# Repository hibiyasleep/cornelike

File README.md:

# Cornel

yet another [Crkbd](https://github.com/foostan/crkbd) clone, but with 5 rows.

---

<details>
<summary> Disclaimer </summary>

 ignore this if you're brave enough, like, if you know what Kailh Choc is, then
you are safe.

>  THIS PROJECT IS CURRENTLY WORK IN PROGRESS, NOTHING IS CLEAR, EVERY SPECIFICA-
> TION and/or DIMENSIONS and/or FEATURES and EVERYTHING MIGHT BE ABLE TO CHANGED
> WITHOUT ANY NOTICE. THIS MIGHT NOT FIT WITH YOUR LASER-ETCHED PLATE. THIS MIGHT
> DOES NOT FIT INTO YOUR $400 ALUMINUM CNC-ANODIZED CORNE CASE. YOUR CR2 BATTERY
> MIGHT BE BLOWN (SURE, I ALSO HAVE THIS RISK IN THIS CASE)
>
>  SO ANYWAY, I, HIBIYA INEMURI, DO NOT HOLD ANY TYPE OF RESPONSIBILITY IN ANY
> CASE.

</details>

## About

 According to [Crkbd](https://github.com/foostan/crkbd), the Corne keyboard is:

>  The Corne keyboard is a split keyboard with 3x6 column staggered keys and 3
> thumb keys, based on Helix. Crkbd stands for Corne Keyboard.

 Corne**l** is basically a clone of Corne keyboard, but with

* **Kailh Choc Switches** but keeping cherry pitch (19mm) for V2 keycaps.
* **Number Row**: to provide easy transition to 40% layout.
  can be removed later if no longer required. (irreversible)
* **Bluetooth MCU Support**: Cornel provides battery board (discharge only)
  that fits onto MCU cover, might be able to power [BLE Micro Pro](https://github.com/sekigon-gonnoc/BLE-Micro-Pro/), etc.
* **Low Profile**: Cornel might do any attempt to reduce thickness of keyboard.
  (TBD)

## Progress

* [ ] PCB
  * [x] Choc (revision: 1)
  * [ ] Cherry
* [ ] Plate
  * [ ] Upper (with acrylic and countersink holes)
  * [ ] Lower
* [ ] Software
  * [x] Arduino Demo (TBA)
  * [ ] QMK support
* [ ] Compability
  * [ ] Classic Pro Micro
  * [ ] [BLE Pro Micro](https://github.com/sekigon-gonnoc/BLE-Micro-Pro)
    * [ ] [LPME-IO](https://github.com/sekigon-gonnoc/LPME-IO)...?
  * [ ] [nice!nano](https://docs.nicekeyboards.com/)
  * [ ] TBA
* [ ] Problems
  * [ ] Detachability of Number row
  * [ ] removing LED Signal Skip jumper (by reordering LEDs)
* [ ] Photos

## Photos

> **WORK IN PROGRESS**

* First prototype (revision 0), with lubed 35g Burnt Orange.

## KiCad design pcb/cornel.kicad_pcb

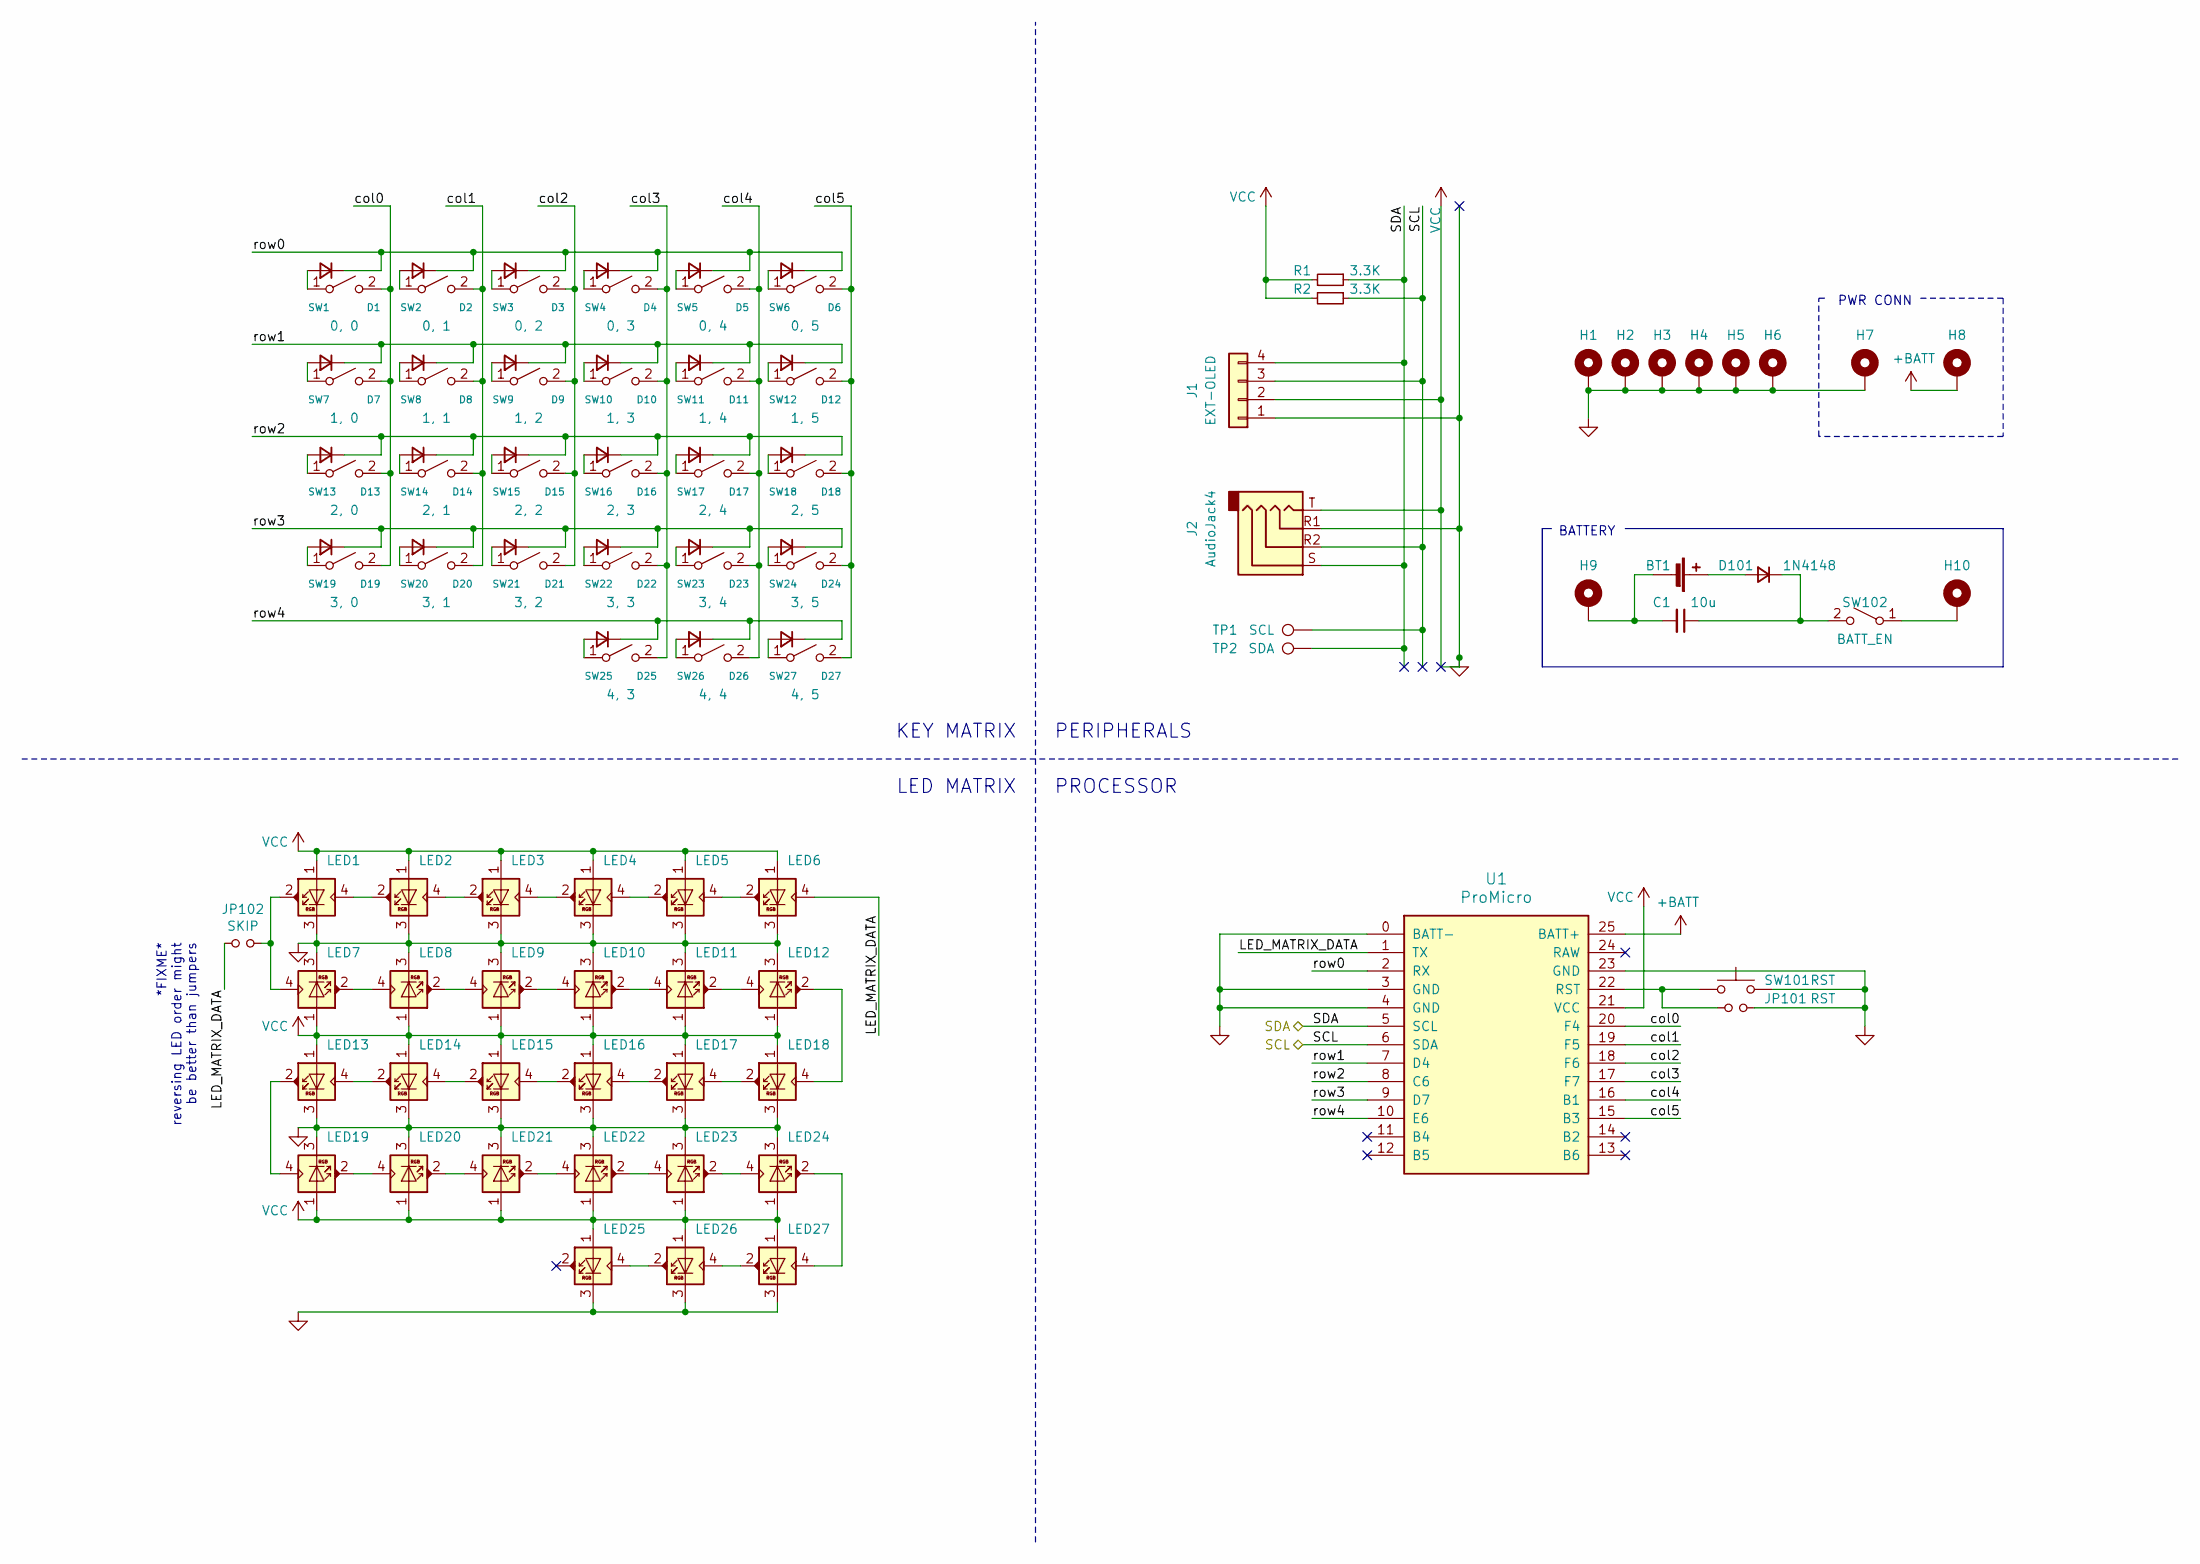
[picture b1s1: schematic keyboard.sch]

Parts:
BT1: CR1632; keystone-1010-mid-mount-cr2
C1: 10u; C_1206_3216Metric
D1, D2, D3, D4, D5, D6, D7, D8, D9, D10, D11, D12, D13, D14, D15, D16, D17, D18, D19, D20, D21, D22, D23, D24, D25, D26, D27, D101: 1N4148; D_1206_3216Metric
H1, H2, H3, H4, H5, H6: MountingHole_Pad; MountingHole_4.1mm_M2-Pillar_Pad
H7, H8, H9, H10: MountingHole_Pad; MountingHole_2.2mm_Via
J1: EXT-OLED; PinHeader_1x04_P2.54mm_Vertical
J2: AudioJack4; Jack_3.5mm_PJ320A_Horizontal
JP101: RST; SolderJumper-2_P1.3mm_Open_Pad1.0x1.5mm
JP102: SKIP; SolderJumper-2_P1.3mm_Open_Pad1.0x1.5mm
LED1, LED2, LED3, LED4, LED5, LED6, LED7, LED8, LED9, LED10, LED11, LED12, LED13, LED14, LED15, LED16, LED17, LED18, LED19, LED20, LED21, LED22, LED23, LED24, LED25, LED26, LED27: SK6812MINI; SK6812MINI-E_InsidePCB_singleside
R1, R2: 3.3K; R_1206_3216Metric
SW1: 0, 0; kailh-pcb-socket-choc-singleside
SW2: 0, 1; kailh-pcb-socket-choc-singleside
SW3: 0, 2; kailh-pcb-socket-choc-singleside
SW4: 0, 3; kailh-pcb-socket-choc-singleside
SW5: 0, 4; kailh-pcb-socket-choc-singleside
SW6: 0, 5; kailh-pcb-socket-choc-singleside
SW7: 1, 0; kailh-pcb-socket-choc-singleside
SW8: 1, 1; kailh-pcb-socket-choc-singleside
SW9: 1, 2; kailh-pcb-socket-choc-singleside
SW10: 1, 3; kailh-pcb-socket-choc-singleside
SW11: 1, 4; kailh-pcb-socket-choc-singleside
SW12: 1, 5; kailh-pcb-socket-choc-singleside
SW13: 2, 0; kailh-pcb-socket-choc-singleside
SW14: 2, 1; kailh-pcb-socket-choc-singleside
SW15: 2, 2; kailh-pcb-socket-choc-singleside
SW16: 2, 3; kailh-pcb-socket-choc-singleside
SW17: 2, 4; kailh-pcb-socket-choc-singleside
SW18: 2, 5; kailh-pcb-socket-choc-singleside
SW19: 3, 0; kailh-pcb-socket-choc-singleside
SW20: 3, 1; kailh-pcb-socket-choc-singleside
SW21: 3, 2; kailh-pcb-socket-choc-singleside
SW22: 3, 3; kailh-pcb-socket-choc-singleside
SW23: 3, 4; kailh-pcb-socket-choc-singleside
SW24: 3, 5; kailh-pcb-socket-choc-singleside
SW25: 4, 3; kailh-pcb-socket-choc-singleside
SW26: 4, 4; kailh-pcb-socket-choc-singleside
SW27: 4, 5; kailh-pcb-socket-choc-singleside
SW101: RST; SW_Push_SPST_NO_Alps_SKRK
SW102: BATT_EN; K3-1296S
TP1: SCL
TP2: SDA
U1: ProMicro; arduino-pro-micro-with-batt

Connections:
+BATT: H8.1, U1.25 (BATT+); also elsewhere on the board
/keyboard-l/LED_MATRIX_DATA: JP102.2, LED6.4 (DIN), U1.1 (TX)
/keyboard-l/SCL: J1.3, J2.R2, R2.1, U1.6 (SDA)
/keyboard-l/SDA: J1.4, J2.S, R1.1, U1.5 (SCL)
/keyboard-l/col0: SW1.2 (B), SW7.2 (B), SW13.2 (B), SW19.2 (B), U1.20 (F4)
/keyboard-l/col1: SW2.2 (B), SW8.2 (B), SW14.2 (B), SW20.2 (B), U1.19 (F5)
/keyboard-l/col2: SW3.2 (B), SW9.2 (B), SW15.2 (B), SW21.2 (B), U1.18 (F6)
/keyboard-l/col3: SW4.2 (B), SW10.2 (B), SW16.2 (B), SW22.2 (B), SW25.2 (B), U1.17 (F7)
/keyboard-l/col4: SW5.2 (B), SW11.2 (B), SW17.2 (B), SW23.2 (B), SW26.2 (B), U1.16 (B1)
/keyboard-l/col5: SW6.2 (B), SW12.2 (B), SW18.2 (B), SW24.2 (B), SW27.2 (B), U1.15 (B3)
/keyboard-l/row0: D1.1 (K), D2.1 (K), D3.1 (K), D4.1 (K), D5.1 (K), D6.1 (K), U1.2 (RX)
/keyboard-l/row1: D7.1 (K), D8.1 (K), D9.1 (K), D10.1 (K), D11.1 (K), D12.1 (K), U1.7 (D4)
/keyboard-l/row2: D13.1 (K), D14.1 (K), D15.1 (K), D16.1 (K), D17.1 (K), D18.1 (K), U1.8 (C6)
/keyboard-l/row3: D19.1 (K), D20.1 (K), D21.1 (K), D22.1 (K), D23.1 (K), D24.1 (K), U1.9 (D7)
/keyboard-l/row4: D25.1 (K), D26.1 (K), D27.1 (K), U1.10 (E6)
unnamed: BT1.1 (+), D101.2 (A)
unnamed: BT1.2 (-), C1.2, H9.1
unnamed: C1.1, D101.1 (K), SW102.2 (B)
unnamed: D1.2 (A), SW1.1 (A)
unnamed: D2.2 (A), SW2.1 (A)
unnamed: D3.2 (A), SW3.1 (A)
unnamed: D4.2 (A), SW4.1 (A)
unnamed: D5.2 (A), SW5.1 (A)
unnamed: D6.2 (A), SW6.1 (A)
unnamed: D7.2 (A), SW7.1 (A)
unnamed: D8.2 (A), SW8.1 (A)
unnamed: D9.2 (A), SW9.1 (A)
unnamed: D10.2 (A), SW10.1 (A)
unnamed: D11.2 (A), SW11.1 (A)
unnamed: D12.2 (A), SW12.1 (A)
unnamed: D13.2 (A), SW13.1 (A)
unnamed: D14.2 (A), SW14.1 (A)
unnamed: D15.2 (A), SW15.1 (A)
unnamed: D16.2 (A), SW16.1 (A)
unnamed: D17.2 (A), SW17.1 (A)
unnamed: D18.2 (A), SW18.1 (A)
unnamed: D19.2 (A), SW19.1 (A)
unnamed: D20.2 (A), SW20.1 (A)
unnamed: D21.2 (A), SW21.1 (A)
unnamed: D22.2 (A), SW22.1 (A)
unnamed: D23.2 (A), SW23.1 (A)
unnamed: D24.2 (A), SW24.1 (A)
unnamed: D25.2 (A), SW25.1 (A)
unnamed: D26.2 (A), SW26.1 (A)
unnamed: D27.2 (A), SW27.1 (A)
unnamed: H10.1, SW102.1 (A)
unnamed: SW101.2, U1.22 (RST)
unnamed: JP102.1, LED1.2 (DOUT), LED7.4 (DIN)
unnamed: LED1.4 (DIN), LED2.2 (DOUT)
unnamed: LED2.4 (DIN), LED3.2 (DOUT)
unnamed: LED3.4 (DIN), LED4.2 (DOUT)
unnamed: LED4.4 (DIN), LED5.2 (DOUT)
unnamed: LED5.4 (DIN), LED6.2 (DOUT)
unnamed: LED7.2 (DOUT), LED8.4 (DIN)
unnamed: LED8.2 (DOUT), LED9.4 (DIN)
unnamed: LED10.2 (DOUT), LED11.4 (DIN)
unnamed: LED9.2 (DOUT), LED10.4 (DIN)
unnamed: LED11.2 (DOUT), LED12.4 (DIN)
unnamed: LED12.2 (DOUT), LED18.4 (DIN)
unnamed: LED13.2 (DOUT), LED19.4 (DIN)
unnamed: LED13.4 (DIN), LED14.2 (DOUT)
unnamed: LED14.4 (DIN), LED15.2 (DOUT)
unnamed: LED15.4 (DIN), LED16.2 (DOUT)
unnamed: LED16.4 (DIN), LED17.2 (DOUT)
unnamed: LED17.4 (DIN), LED18.2 (DOUT)
unnamed: LED19.2 (DOUT), LED20.4 (DIN)
unnamed: LED20.2 (DOUT), LED21.4 (DIN)
unnamed: LED21.2 (DOUT), LED22.4 (DIN)
unnamed: LED22.2 (DOUT), LED23.4 (DIN)
unnamed: LED23.2 (DOUT), LED24.4 (DIN)
unnamed: LED24.2 (DOUT), LED27.4 (DIN)
unnamed: LED25.4 (DIN), LED26.2 (DOUT)
unnamed: LED26.4 (DIN), LED27.2 (DOUT)

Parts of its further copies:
BT2, BT3: CR1632; keystone-1010-mid-mount-cr2
C2: 10u; C_1206_3216Metric
D28, D29, D30, D31, D32, D33, D34, D35, D36, D37, D38, D39, D40, D41, D42, D43, D44, D45, D46, D47, D48, D49, D50, D51, D52, D53, D54, D201: 1N4148; D_1206_3216Metric
H11, H12, H13, H14, H15, H16: MountingHole_Pad; MountingHole_4.1mm_M2-Pillar_Pad
H17, H18, H19, H20: MountingHole_Pad; MountingHole_2.2mm_Via
J3: EXT-OLED; PinHeader_1x04_P2.54mm_Vertical
J4: AudioJack4; Jack_3.5mm_PJ320A_Horizontal
JP201: RST; SolderJumper-2_P1.3mm_Open_Pad1.0x1.5mm
JP202: SKIP; SolderJumper-2_P1.3mm_Open_Pad1.0x1.5mm
LED28, LED29, LED30, LED31, LED32, LED33, LED34, LED35, LED36, LED37, LED38, LED39, LED40, LED41, LED42, LED43, LED44, LED45, LED46, LED47, LED48, LED49, LED50, LED51, LED52, LED53, LED54: SK6812MINI; SK6812MINI-E_InsidePCB_singleside
R3, R4: 3.3K; R_1206_3216Metric
SW28: 0, 0; kailh-pcb-socket-choc-singleside
SW29: 0, 1; kailh-pcb-socket-choc-singleside
SW30: 0, 2; kailh-pcb-socket-choc-singleside
SW31: 0, 3; kailh-pcb-socket-choc-singleside
SW32: 0, 4; kailh-pcb-socket-choc-singleside
SW33: 0, 5; kailh-pcb-socket-choc-singleside
SW34: 1, 0; kailh-pcb-socket-choc-singleside
SW35: 1, 1; kailh-pcb-socket-choc-singleside
SW36: 1, 2; kailh-pcb-socket-choc-singleside
SW37: 1, 3; kailh-pcb-socket-choc-singleside
SW38: 1, 4; kailh-pcb-socket-choc-singleside
SW39: 1, 5; kailh-pcb-socket-choc-singleside
SW40: 2, 0; kailh-pcb-socket-choc-singleside
SW41: 2, 1; kailh-pcb-socket-choc-singleside
SW42: 2, 2; kailh-pcb-socket-choc-singleside
SW43: 2, 3; kailh-pcb-socket-choc-singleside
SW44: 2, 4; kailh-pcb-socket-choc-singleside
SW45: 2, 5; kailh-pcb-socket-choc-singleside
SW46: 3, 0; kailh-pcb-socket-choc-singleside
SW47: 3, 1; kailh-pcb-socket-choc-singleside
SW48: 3, 2; kailh-pcb-socket-choc-singleside
SW49: 3, 3; kailh-pcb-socket-choc-singleside
SW50: 3, 4; kailh-pcb-socket-choc-singleside
SW51: 3, 5; kailh-pcb-socket-choc-singleside
SW52: 4, 3; kailh-pcb-socket-choc-singleside
SW53: 4, 4; kailh-pcb-socket-choc-singleside
SW54: 4, 5; kailh-pcb-socket-choc-singleside
SW201: RST; SW_Push_SPST_NO_Alps_SKRK
SW202: BATT_EN; K3-1296S
TP3: SCL
TP4: SDA
U2: ProMicro; arduino-pro-micro-with-batt

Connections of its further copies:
+BATT: H18.1, U2.25 (BATT+); also elsewhere on the board
/keyboard-r/LED_MATRIX_DATA: JP202.2, LED33.4 (DIN), U2.1 (TX)
/keyboard-r/SCL: J3.3, J4.R2, R4.1, U2.6 (SDA)
/keyboard-r/SDA: J3.4, J4.S, R3.1, U2.5 (SCL)
/keyboard-r/col0: SW28.2 (B), SW34.2 (B), SW40.2 (B), SW46.2 (B), U2.20 (F4)
/keyboard-r/col1: SW29.2 (B), SW35.2 (B), SW41.2 (B), SW47.2 (B), U2.19 (F5)
/keyboard-r/col2: SW30.2 (B), SW36.2 (B), SW42.2 (B), SW48.2 (B), U2.18 (F6)
/keyboard-r/col3: SW31.2 (B), SW37.2 (B), SW43.2 (B), SW49.2 (B), SW52.2 (B), U2.17 (F7)
/keyboard-r/col4: SW32.2 (B), SW38.2 (B), SW44.2 (B), SW50.2 (B), SW53.2 (B), U2.16 (B1)
/keyboard-r/col5: SW33.2 (B), SW39.2 (B), SW45.2 (B), SW51.2 (B), SW54.2 (B), U2.15 (B3)
/keyboard-r/row0: D28.1 (K), D29.1 (K), D30.1 (K), D31.1 (K), D32.1 (K), D33.1 (K), U2.2 (RX)
/keyboard-r/row1: D34.1 (K), D35.1 (K), D36.1 (K), D37.1 (K), D38.1 (K), D39.1 (K), U2.7 (D4)
/keyboard-r/row2: D40.1 (K), D41.1 (K), D42.1 (K), D43.1 (K), D44.1 (K), D45.1 (K), U2.8 (C6)
/keyboard-r/row3: D46.1 (K), D47.1 (K), D48.1 (K), D49.1 (K), D50.1 (K), D51.1 (K), U2.9 (D7)
/keyboard-r/row4: D52.1 (K), D53.1 (K), D54.1 (K), U2.10 (E6)
unnamed: BT2.1 (+), D201.2 (A)
unnamed: BT2.2 (-), C2.2, H19.1
unnamed: C2.1, D201.1 (K), SW202.2 (B)
unnamed: D28.2 (A), SW28.1 (A)
unnamed: D29.2 (A), SW29.1 (A)
unnamed: D30.2 (A), SW30.1 (A)
unnamed: D31.2 (A), SW31.1 (A)
unnamed: D32.2 (A), SW32.1 (A)
unnamed: D33.2 (A), SW33.1 (A)
unnamed: D34.2 (A), SW34.1 (A)
unnamed: D35.2 (A), SW35.1 (A)
unnamed: D36.2 (A), SW36.1 (A)
unnamed: D37.2 (A), SW37.1 (A)
unnamed: D38.2 (A), SW38.1 (A)
unnamed: D39.2 (A), SW39.1 (A)
unnamed: D40.2 (A), SW40.1 (A)
unnamed: D41.2 (A), SW41.1 (A)
unnamed: D42.2 (A), SW42.1 (A)
unnamed: D43.2 (A), SW43.1 (A)
unnamed: D44.2 (A), SW44.1 (A)
unnamed: D45.2 (A), SW45.1 (A)
unnamed: D46.2 (A), SW46.1 (A)
unnamed: D47.2 (A), SW47.1 (A)
unnamed: D48.2 (A), SW48.1 (A)
unnamed: D49.2 (A), SW49.1 (A)
unnamed: D50.2 (A), SW50.1 (A)
unnamed: D51.2 (A), SW51.1 (A)
unnamed: D52.2 (A), SW52.1 (A)
unnamed: D53.2 (A), SW53.1 (A)
unnamed: D54.2 (A), SW54.1 (A)
unnamed: H20.1, SW202.1 (A)
unnamed: SW201.2, U2.22 (RST)
unnamed: JP202.1, LED28.2 (DOUT), LED34.4 (DIN)
unnamed: LED28.4 (DIN), LED29.2 (DOUT)
unnamed: LED29.4 (DIN), LED30.2 (DOUT)
unnamed: LED30.4 (DIN), LED31.2 (DOUT)
unnamed: LED31.4 (DIN), LED32.2 (DOUT)
unnamed: LED32.4 (DIN), LED33.2 (DOUT)
unnamed: LED34.2 (DOUT), LED35.4 (DIN)
unnamed: LED35.2 (DOUT), LED36.4 (DIN)
unnamed: LED36.2 (DOUT), LED37.4 (DIN)
unnamed: LED37.2 (DOUT), LED38.4 (DIN)
unnamed: LED38.2 (DOUT), LED39.4 (DIN)
unnamed: LED39.2 (DOUT), LED45.4 (DIN)
unnamed: LED40.2 (DOUT), LED46.4 (DIN)
unnamed: LED40.4 (DIN), LED41.2 (DOUT)
unnamed: LED41.4 (DIN), LED42.2 (DOUT)
unnamed: LED42.4 (DIN), LED43.2 (DOUT)
unnamed: LED43.4 (DIN), LED44.2 (DOUT)
unnamed: LED44.4 (DIN), LED45.2 (DOUT)
unnamed: LED46.2 (DOUT), LED47.4 (DIN)
unnamed: LED47.2 (DOUT), LED48.4 (DIN)
unnamed: LED48.2 (DOUT), LED49.4 (DIN)
unnamed: LED49.2 (DOUT), LED50.4 (DIN)
unnamed: LED50.2 (DOUT), LED51.4 (DIN)
unnamed: LED51.2 (DOUT), LED54.4 (DIN)
unnamed: LED52.4 (DIN), LED53.2 (DOUT)
unnamed: LED53.4 (DIN), LED54.2 (DOUT)

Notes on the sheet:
*FIXME* reversing LED order might be better than jumpers
BATTERY
PWR CONN
PERIPHERALS
LED MATRIX
PROCESSOR
KEY MATRIX

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
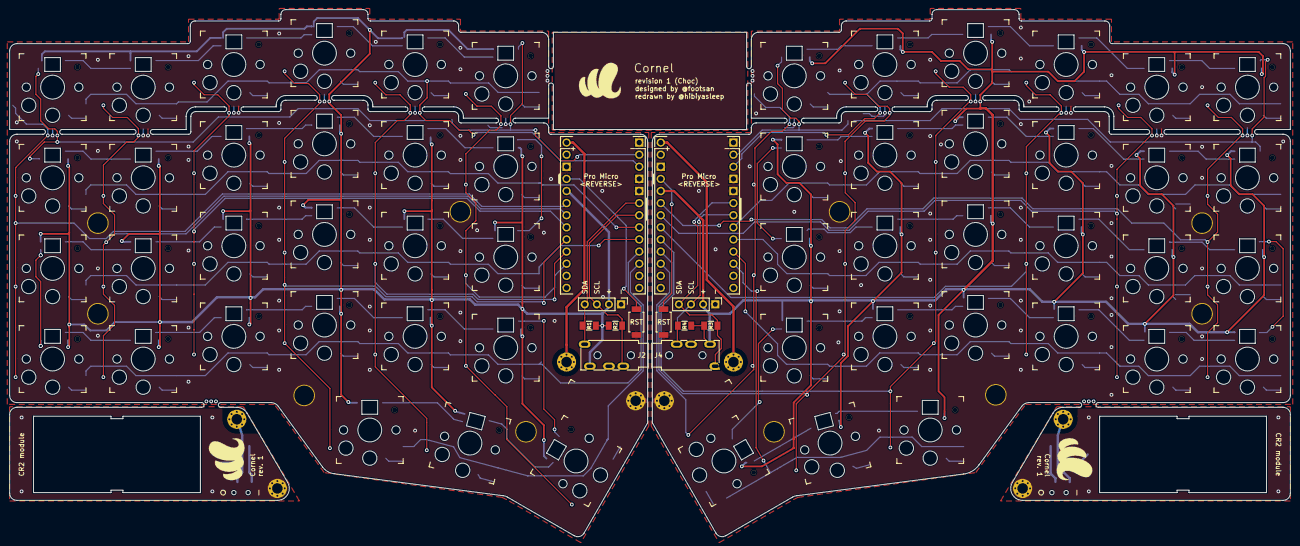
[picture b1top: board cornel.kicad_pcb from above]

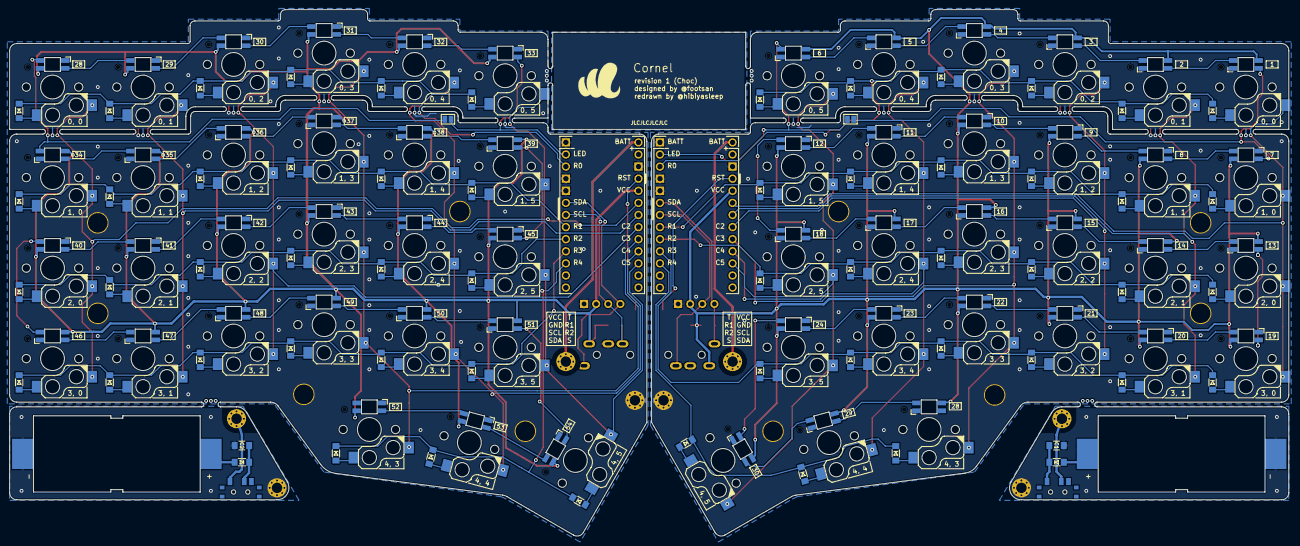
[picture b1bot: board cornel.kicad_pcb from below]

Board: 2 copper layers, 268.4 x 110.4 mm, 202 parts (66 on the bottom side), 147 nets.

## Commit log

2021-03-05 initial empty commit
2021-03-05 pcb: initial commit
2021-03-05 pcb: cleanup & added schematics.pdf
2021-03-05 README: initial commit
2021-03-05 Cornel PCB version r1
2021-03-05 README: update about batteries
